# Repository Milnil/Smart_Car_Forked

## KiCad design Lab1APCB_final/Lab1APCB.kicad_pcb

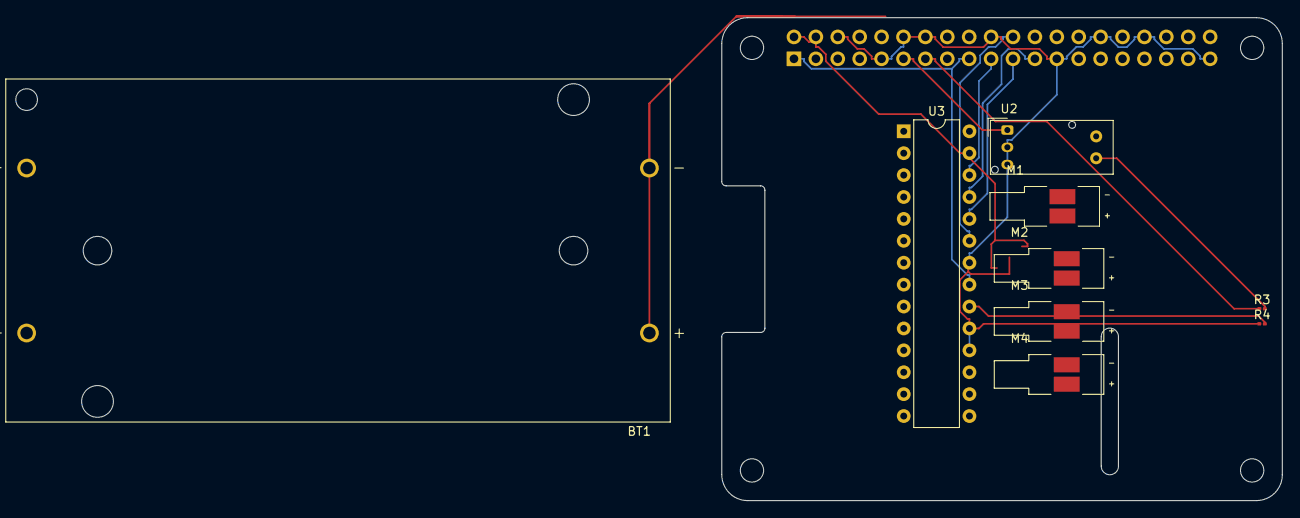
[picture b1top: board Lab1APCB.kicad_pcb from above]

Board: 2 copper layers, 65.0 x 56.0 mm, 14 parts (1 on the bottom side), 11 nets.

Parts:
BT1: 1049; BAT_1049
J1: GPIO; PinSocket_2x20_P2.54mm_Vertical
M1, M2, M3, M4: Motor_DC; PUI_HD-EMB1305-SC
MH1, MH2, MH3, MH4: MountingHole_2.7mm_M2.5
R3, R4: 10k; R_0201_0603Metric
U2: LG206D; Kodenshi_LG206D
U3: TLC5940NT; DIP-28_W7.62mm

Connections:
+3V3: J1.1, J1.17, U3.21 (VCC)
+5V: BT1.N2, BT1.P1, J1.2, J1.4, U3.27 (VPRG)
/GPIO9/SPI0.MISO: J1.21, U3.24 (XLAT)
/GPIO10/SPI0.MOSI: J1.19, U3.26 (SIN)
/GPIO11/SPI0.SCLK: J1.23, U3.25 (SCLK)
/GPIO17: J1.11, U2.1 (VCC)
/GPIO25: J1.22, U3.23 (BLANK)
/GPIO27: J1.13, R3.1
GND: BT1.N1, BT1.P2, J1.6, J1.9, J1.12, J1.14, J1.20, J1.25, J1.30, J1.34, J1.39, R4.1, U2.2 (VOUT), U2.3 (GND), U3.18 (GSCLK), U3.19 (DCPRG), U3.22 (GND)
unnamed: R3.2, U2.4 (A)
unnamed: R4.2, U3.20 (IREF)

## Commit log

2024-09-14 Added script for Lab
2024-09-15 Redundant continue in main run function; Pushed PCB
2024-09-18 servo edit
2024-09-19 Added picamera script
2024-09-19 added tensorflow setupscript
2024-09-19 added setup
2024-09-19 Added object detection
2024-09-19 added img.py
2024-09-20 training data
2024-09-20 premapping - proly gud; mapping idk
2024-09-20 gogo
2024-09-20 asdfa
2024-09-20 new file ayush code
2024-09-20 mapping updates
2024-09-20 gitignore update
2024-09-20 Added object detection class
2024-09-20 Updated detection threshold for traffic light
2024-09-21 Fixed advanced mapping with dynamic moving and pathplanning using A* and padding for collisions. The A* may be kinda slow... not sure how it will work IRL. I made Mock classes for the Car modules, it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
    mappings/AdvancedMapping folder has pictures of a basic mapping Mock env using full 180 degree scanning at 1 degree intervals, then the same situation using interpolation at 6 degree intervals.
    mappings/Routing has a full path planning with interpolation and movement shown by steps.
2024-09-21 Fixed graph bug
2024-09-21 Downsized map to 100x100. Improved mapping visualization and fixed dimensions
2024-09-21 replaced mock with car componenets
2024-09-21 sdfg
2024-09-21 works ofc
2024-09-22 mapping edit
2024-09-22 works definitely!
2024-09-22 asdf
2024-09-22 most recent mapping changes
2024-09-22 course
2024-09-22 course 1 complete
2024-09-22 edit to detection threshold
2024-09-22 Added course 3
2024-09-22 mapping demo code
2024-10-12 lab2 stuff
2024-10-12 from pi
2024-10-12 yippee
2024-10-12 working
2024-10-13 added code to fix camera
2024-10-13 uncommented the servo code
2024-10-13 added bluetooth
2024-10-31 added lab3 code
2024-11-01 new log
